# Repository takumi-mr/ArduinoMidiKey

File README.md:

# ArduinoMidiKey
Make midi keyboard (controller) with Arduino.  
You can use switchs as a midi controller.  
Support Octave-Transport and Pitch-Shift.  
If arrange switchs like piano keyboard, you can make midi keyboard.  
Or arrange grid, you can make drampad.

In default,  
* 4 * 4 grid (16 pcs) switchs use as keyboard. (You can change size of pad editting code)
* PIN{ 4, 5, 6, 7 } use as output pins.
* PIN{ 8, 9, 10, 11 } use as input pins.

# Requirements  

* Arduino need something MIDI interface, eg MIDI Shield or [USB-MIDI](https://github.com/kuwatay/mocolufa) .
  * If Use USB-MIDI, you need to flash firmware to Atmega16u2 using [dfu-programmer](https://dfu-programmer.github.io/) or [Atmel FLIP](https://www.microchip.com/DevelopmentTools/ProductDetails/PartNO/FLIP).
* [MIDI Library](https://playground.arduino.cc/Main/MIDILibrary/) 4.3.1

# How to use  

1. Write sketch to Arduino.  
1. Make grid array of switch.  
1. Connect cable to switch.

※To write sketch, you need to jumper ISP,Otherwise your Arduino are detected as MIDI device so that can't write sketch.

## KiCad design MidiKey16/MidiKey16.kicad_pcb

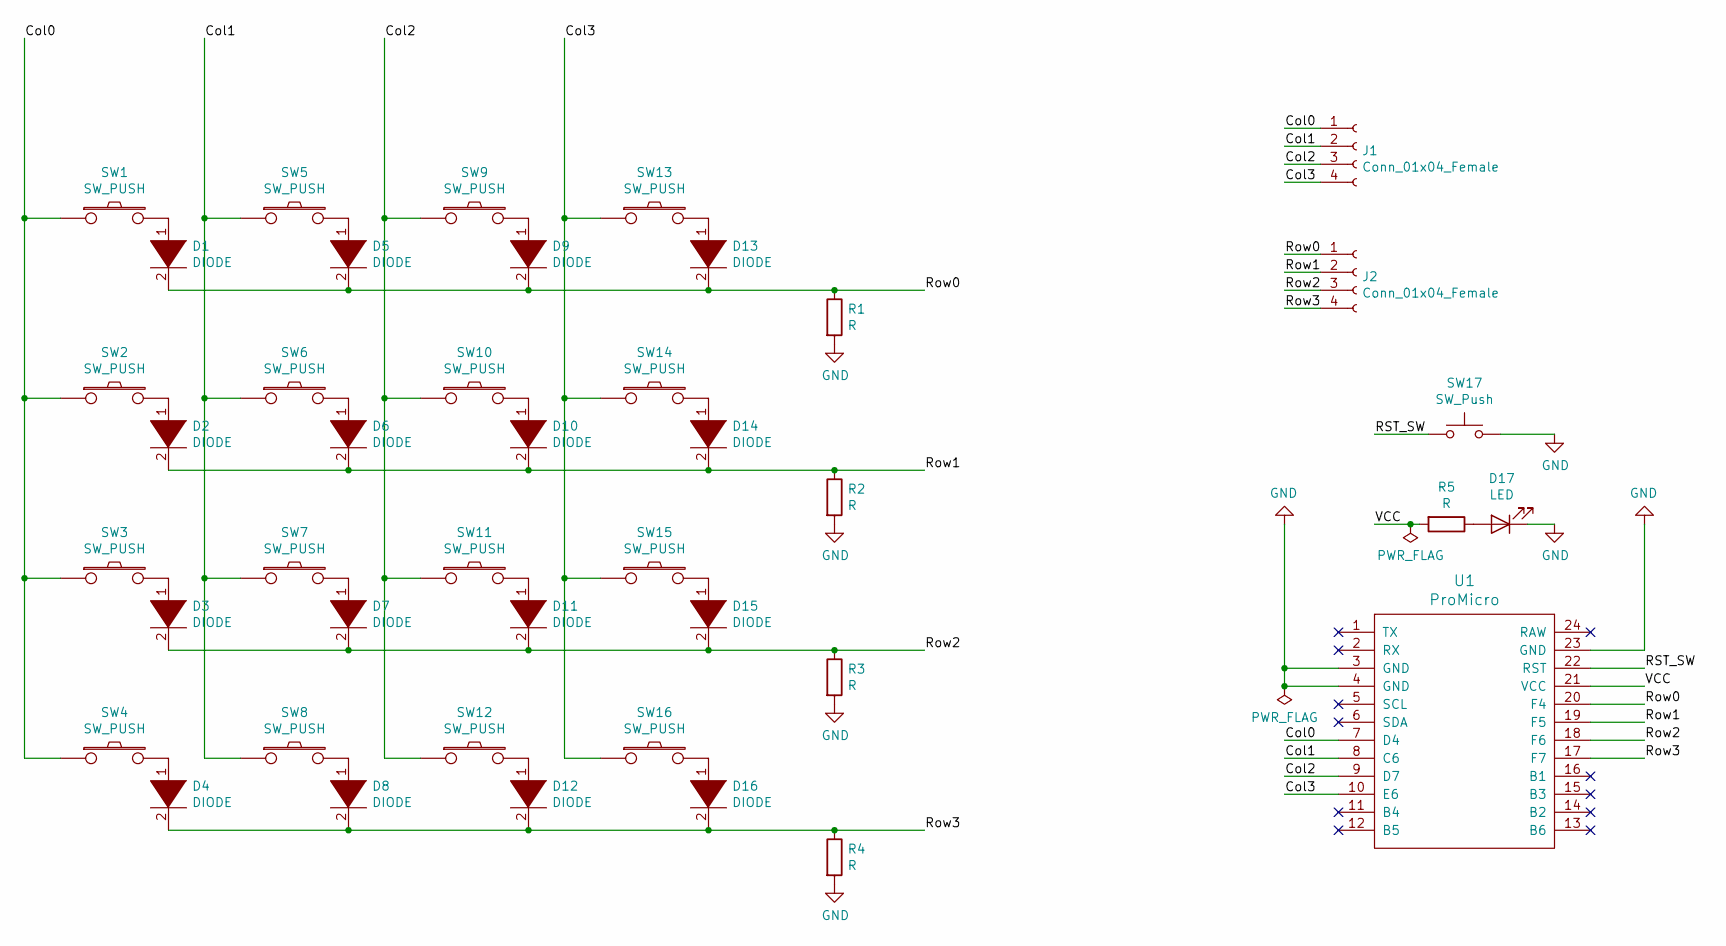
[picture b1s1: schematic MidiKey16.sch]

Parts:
D1, D2, D3, D4, D5, D6, D7, D8, D9, D10, D11, D12, D13, D14, D15, D16: DIODE; D_A-405_P7.62mm_Horizontal
D17: LED; LED_D5.0mm
J1, J2: Conn_01x04_Female; PinSocket_1x04_P2.54mm_Vertical
R1, R2, R3, R4, R5: R; R_Axial_DIN0207_L6.3mm_D2.5mm_P7.62mm_Horizontal
SW1, SW2, SW3, SW4, SW5, SW6, SW7, SW8, SW9, SW10, SW11, SW12, SW13, SW14, SW15, SW16: SW_PUSH; SW_Cherry_MX_1.00u_PCB
SW17: SW_Push; SW_PUSH_6mm
U1: ProMicro; Pro_Micro

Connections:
/Col0: J1.1, SW1.1, SW2.1, SW3.1, SW4.1, U1.7 (D4)
/Col1: J1.2, SW5.1, SW6.1, SW7.1, SW8.1, U1.8 (C6)
/Col2: J1.3, SW9.1, SW10.1, SW11.1, SW12.1, U1.9 (D7)
/Col3: J1.4, SW13.1, SW14.1, SW15.1, SW16.1, U1.10 (E6)
/RST_SW: SW17.1, U1.22 (RST)
/Row0: D1.2 (A), D5.2 (A), D9.2 (A), D13.2 (A), J2.1, R1.1, U1.20 (F4)
/Row1: D2.2 (A), D6.2 (A), D10.2 (A), D14.2 (A), J2.2, R2.1, U1.19 (F5)
/Row2: D3.2 (A), D7.2 (A), D11.2 (A), D15.2 (A), J2.3, R3.1, U1.18 (F6)
/Row3: D4.2 (A), D8.2 (A), D12.2 (A), D16.2 (A), J2.4, R4.1, U1.17 (F7)
/VCC: R5.2, U1.21 (VCC)
GND: D17.1 (K), R1.2, R2.2, R3.2, R4.2, SW17.2, U1.3 (GND), U1.4 (GND), U1.23 (GND)
unnamed: D1.1 (K), SW1.2
unnamed: D2.1 (K), SW2.2
unnamed: D3.1 (K), SW3.2
unnamed: D4.1 (K), SW4.2
unnamed: D5.1 (K), SW5.2
unnamed: D6.1 (K), SW6.2
unnamed: D7.1 (K), SW7.2
unnamed: D8.1 (K), SW8.2
unnamed: D9.1 (K), SW9.2
unnamed: D10.1 (K), SW10.2
unnamed: D11.1 (K), SW11.2
unnamed: D12.1 (K), SW12.2
unnamed: D13.1 (K), SW13.2
unnamed: D14.1 (K), SW14.2
unnamed: D15.1 (K), SW15.2
unnamed: D16.1 (K), SW16.2
unnamed: D17.2 (A), R5.1

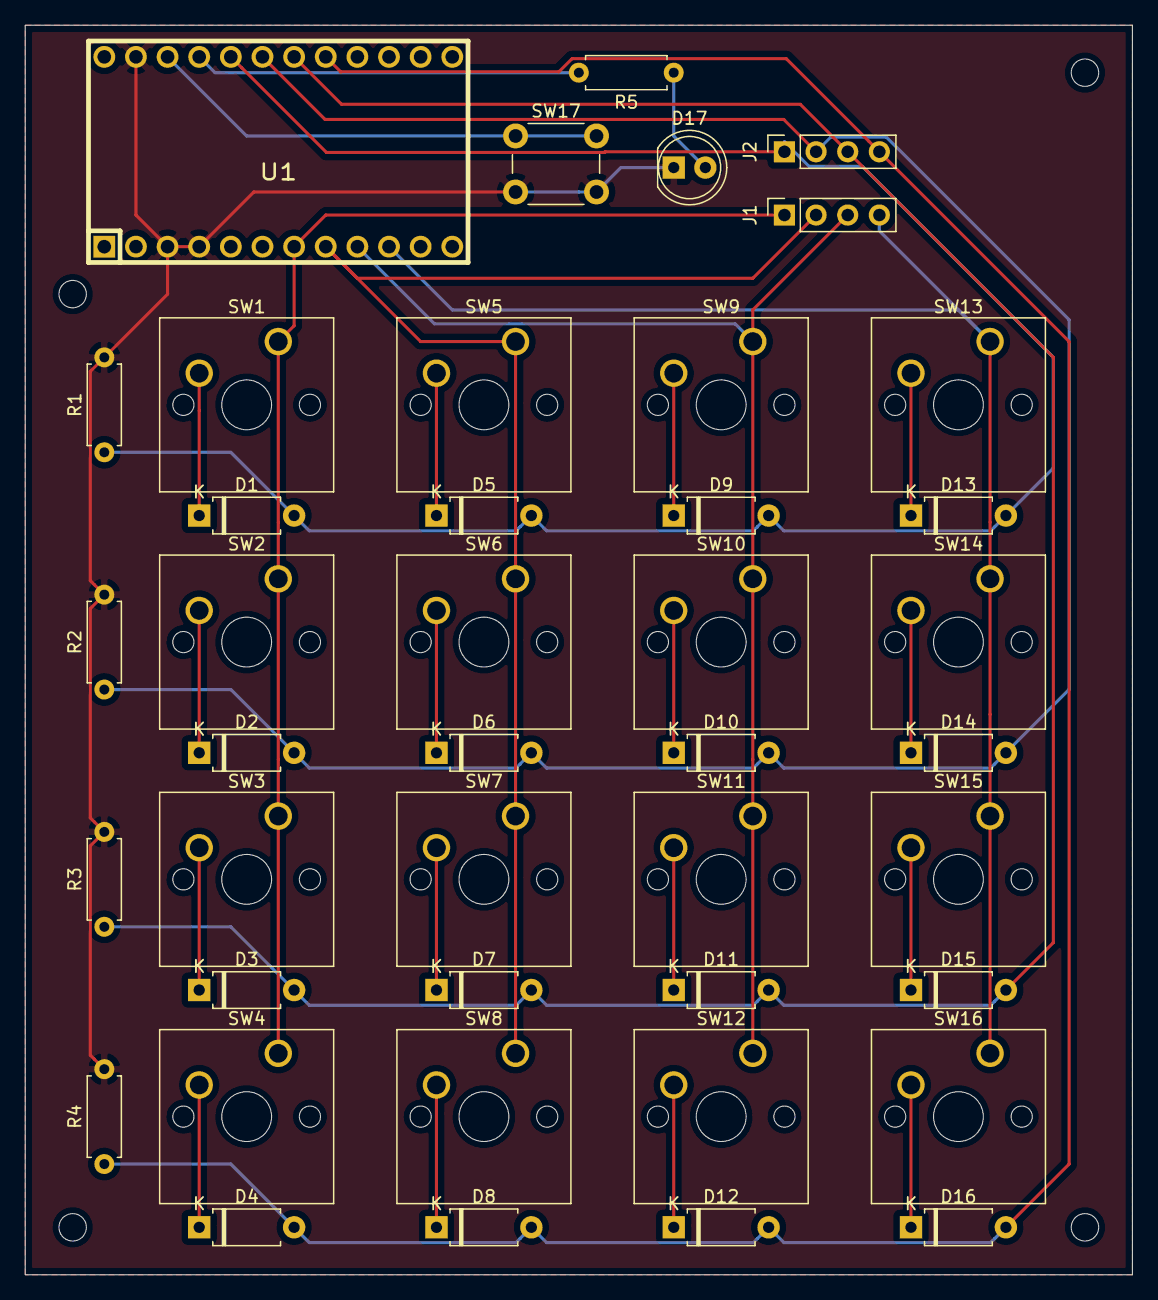
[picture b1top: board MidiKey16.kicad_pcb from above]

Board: 2 copper layers, 88.9 x 100.3 mm, 42 parts (0 on the bottom side), 28 nets.

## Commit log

2020-01-01 Create LICENSE
